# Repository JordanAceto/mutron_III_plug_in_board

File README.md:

# NOTE: development of all VCF plug-in boards has been moved here https://github.com/JordanAceto/VCF_plug_in_boards
### This repo will no longer be updated. Follow the above link for the most current files.

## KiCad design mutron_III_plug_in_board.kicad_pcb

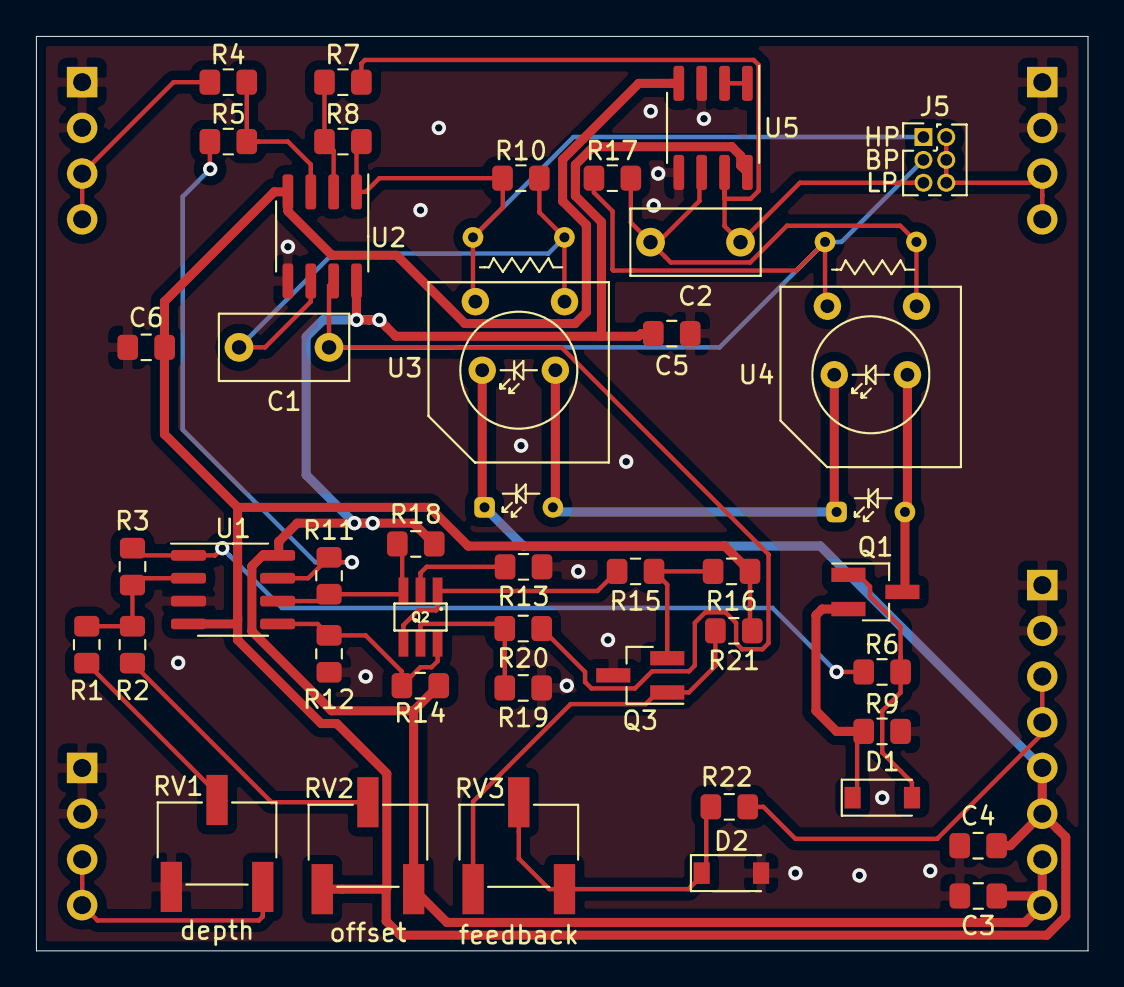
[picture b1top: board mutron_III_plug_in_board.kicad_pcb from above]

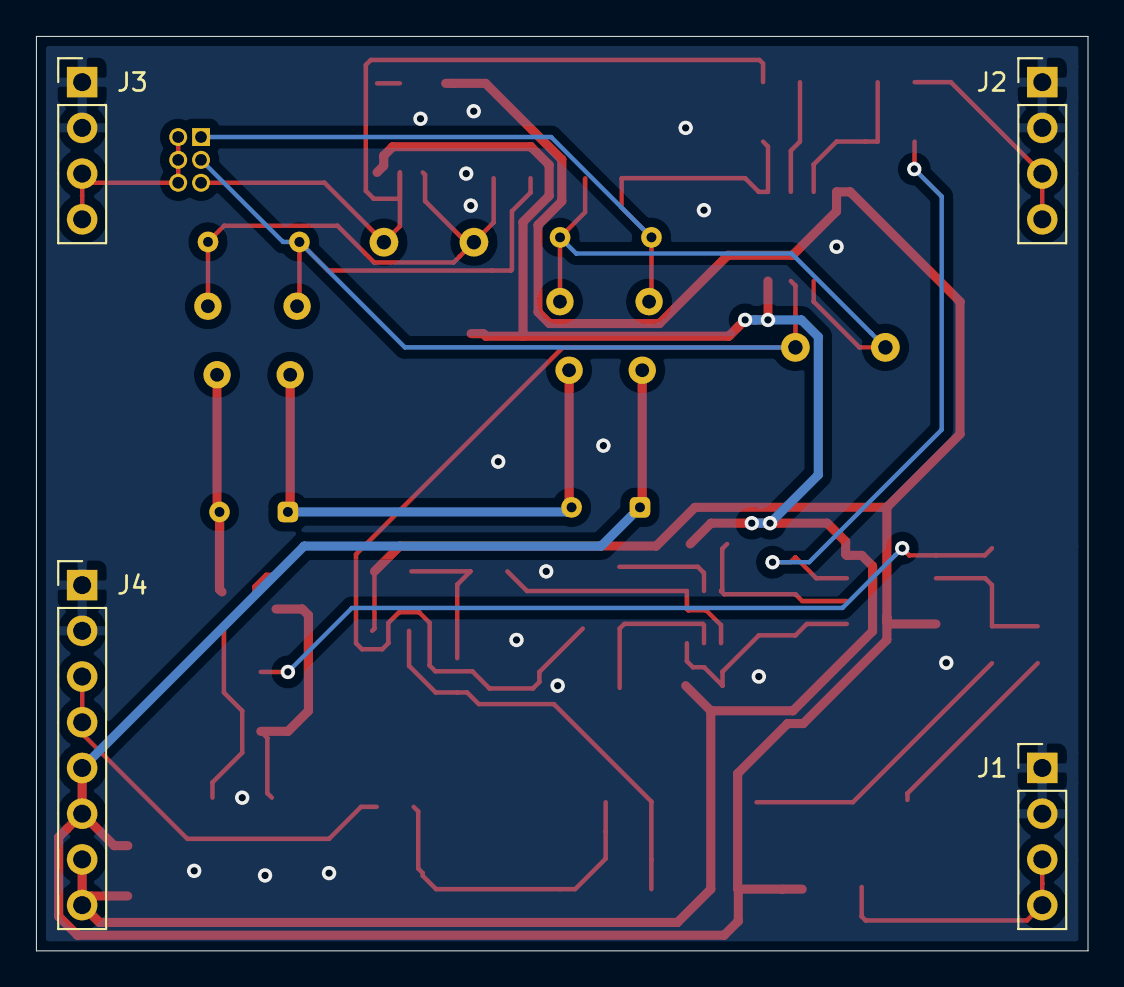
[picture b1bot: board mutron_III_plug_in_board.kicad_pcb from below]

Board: 2 copper layers, 58.4 x 50.8 mm, 46 parts (4 on the bottom side), 32 nets.

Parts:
C1, C2: 47nF; C_Rect_L7.0mm_W3.5mm_P5.00mm
C3, C4, C5, C6: 100nF; C_0805_2012Metric_Pad1.15x1.40mm_HandSolder
D1: 1N914; D_SOD-123
D2: 1N5225B; D_SOD-123
J1, J2, J3: Conn_01x04_Male; PinHeader_1x04_P2.54mm_Vertical
J4: Conn_01x08_Male; PinHeader_1x08_P2.54mm_Vertical
J5: HP-BP-LP; PinHeader_2x03_P1.27mm_Vertical
Q1: BC857; SOT-23_Handsoldering
Q2: BCM847; SOT457
Q3: BC847; SOT-23_Handsoldering
R1: 68k; R_0805_2012Metric_Pad1.15x1.40mm_HandSolder
R2: 1M; R_0805_2012Metric_Pad1.15x1.40mm_HandSolder
R3, R11, R12, R20: 100k; R_0805_2012Metric_Pad1.15x1.40mm_HandSolder
R4, R5, R6: 10k; R_0805_2012Metric_Pad1.15x1.40mm_HandSolder
R7, R8: 22k; R_0805_2012Metric_Pad1.15x1.40mm_HandSolder
R9: 100; R_0805_2012Metric_Pad1.15x1.40mm_HandSolder
R10, R17: 680k; R_0805_2012Metric_Pad1.15x1.40mm_HandSolder
R13, R19: 1k; R_0805_2012Metric_Pad1.15x1.40mm_HandSolder
R14, R16, R18: 15k; R_0805_2012Metric_Pad1.15x1.40mm_HandSolder
R15: 33k; R_0805_2012Metric_Pad1.15x1.40mm_HandSolder
R21: 220k; R_0805_2012Metric_Pad1.15x1.40mm_HandSolder
R22: 7k5; R_0805_2012Metric_Pad1.15x1.40mm_HandSolder
RV1: 10k; Potentiometer_Bourns_3269W_Vertical
RV2, RV3: 100k; Potentiometer_Bourns_3269W_Vertical
U1: TL072; SOIC-8_3.9x4.9mm_P1.27mm
U2, U5: RC4558; SOIC-8_3.9x4.9mm_P1.27mm
U3, U4: vactrol; vactrol_dual_footprint

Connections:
+12V: C3.1, C5.1, J4.7, J4.8, R14.2, R18.2, RV2.3, U1.8, U2.8, U5.8
-12V: C4.2, C6.2, J4.5, J4.6, R16.1, R21.2, RV2.1, U1.4, U2.4, U3.1, U5.4
/I_LED: Q1.3, U4.2
/band_pass: C1.1, J5.3, R17.2, R20.2, U2.7, U4.3
/high_pass: J5.1, R8.1, R10.2, U2.1, U3.3
/low_pass: C2.1, J5.5, R7.1, U5.7
GND: C3.2, C4.1, C5.2, C6.1, D2.2, J1.1, J1.2, J2.1, J2.2, J3.1, J3.2, J4.1, J4.2, Q3.3, R9.1, R12.1, R13.1, R19.1, RV1.1, U1.3, U2.5, U5.3, U5.5
unnamed: C1.2, R10.1, U2.6, U3.4
unnamed: C2.2, R17.1, U4.4, U5.6
unnamed: D1.1, Q1.2, R9.2
unnamed: D1.2, Q1.1, R6.1
unnamed: D2.1, R22.2, RV3.2, RV3.3
unnamed: J1.3, J1.4, RV1.3
unnamed: J2.3, J2.4, R4.2
unnamed: J3.3, J3.4, J5.2, J5.4, J5.6
unnamed: J4.3, J4.4, R22.1
unnamed: Q2.1, Q2.4, R15.2
unnamed: Q2.2, R13.2
unnamed: Q2.3, R11.2, R18.1, U1.6
unnamed: Q2.5, R19.2, R20.1
unnamed: Q2.6, R12.2, R14.1, U1.5
unnamed: Q3.1, R21.1, RV3.1
unnamed: Q3.2, R15.1, R16.2
unnamed: R1.1, R2.1, R3.2, U1.2
unnamed: R1.2, RV1.2
unnamed: R2.2, RV2.2
unnamed: R3.1, R6.2, U1.1
unnamed: R4.1, R5.1, U2.3
unnamed: R7.2, R8.2, U2.2
unnamed: R5.2, R11.1, U1.7
unnamed: U3.2, U4.1
unnamed: U5.1, U5.2

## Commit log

2019-07-10 restructure folders
2019-07-10 change trimmers to cheaper TH type
2020-08-01 add readme with link to new repo
